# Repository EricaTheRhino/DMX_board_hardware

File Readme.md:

Hardware designs for Erica led controller
=========================================

Designs where made in eagle 6.4

Jumper options
--------------

SJ1/SJ2 used for DMX passthough if not populating second rs485 converter (U3)
SJ3 used for linking logic and led power systems together for use with a single power supply
SJ4 links return serial from TLC5940 to avr if wanted

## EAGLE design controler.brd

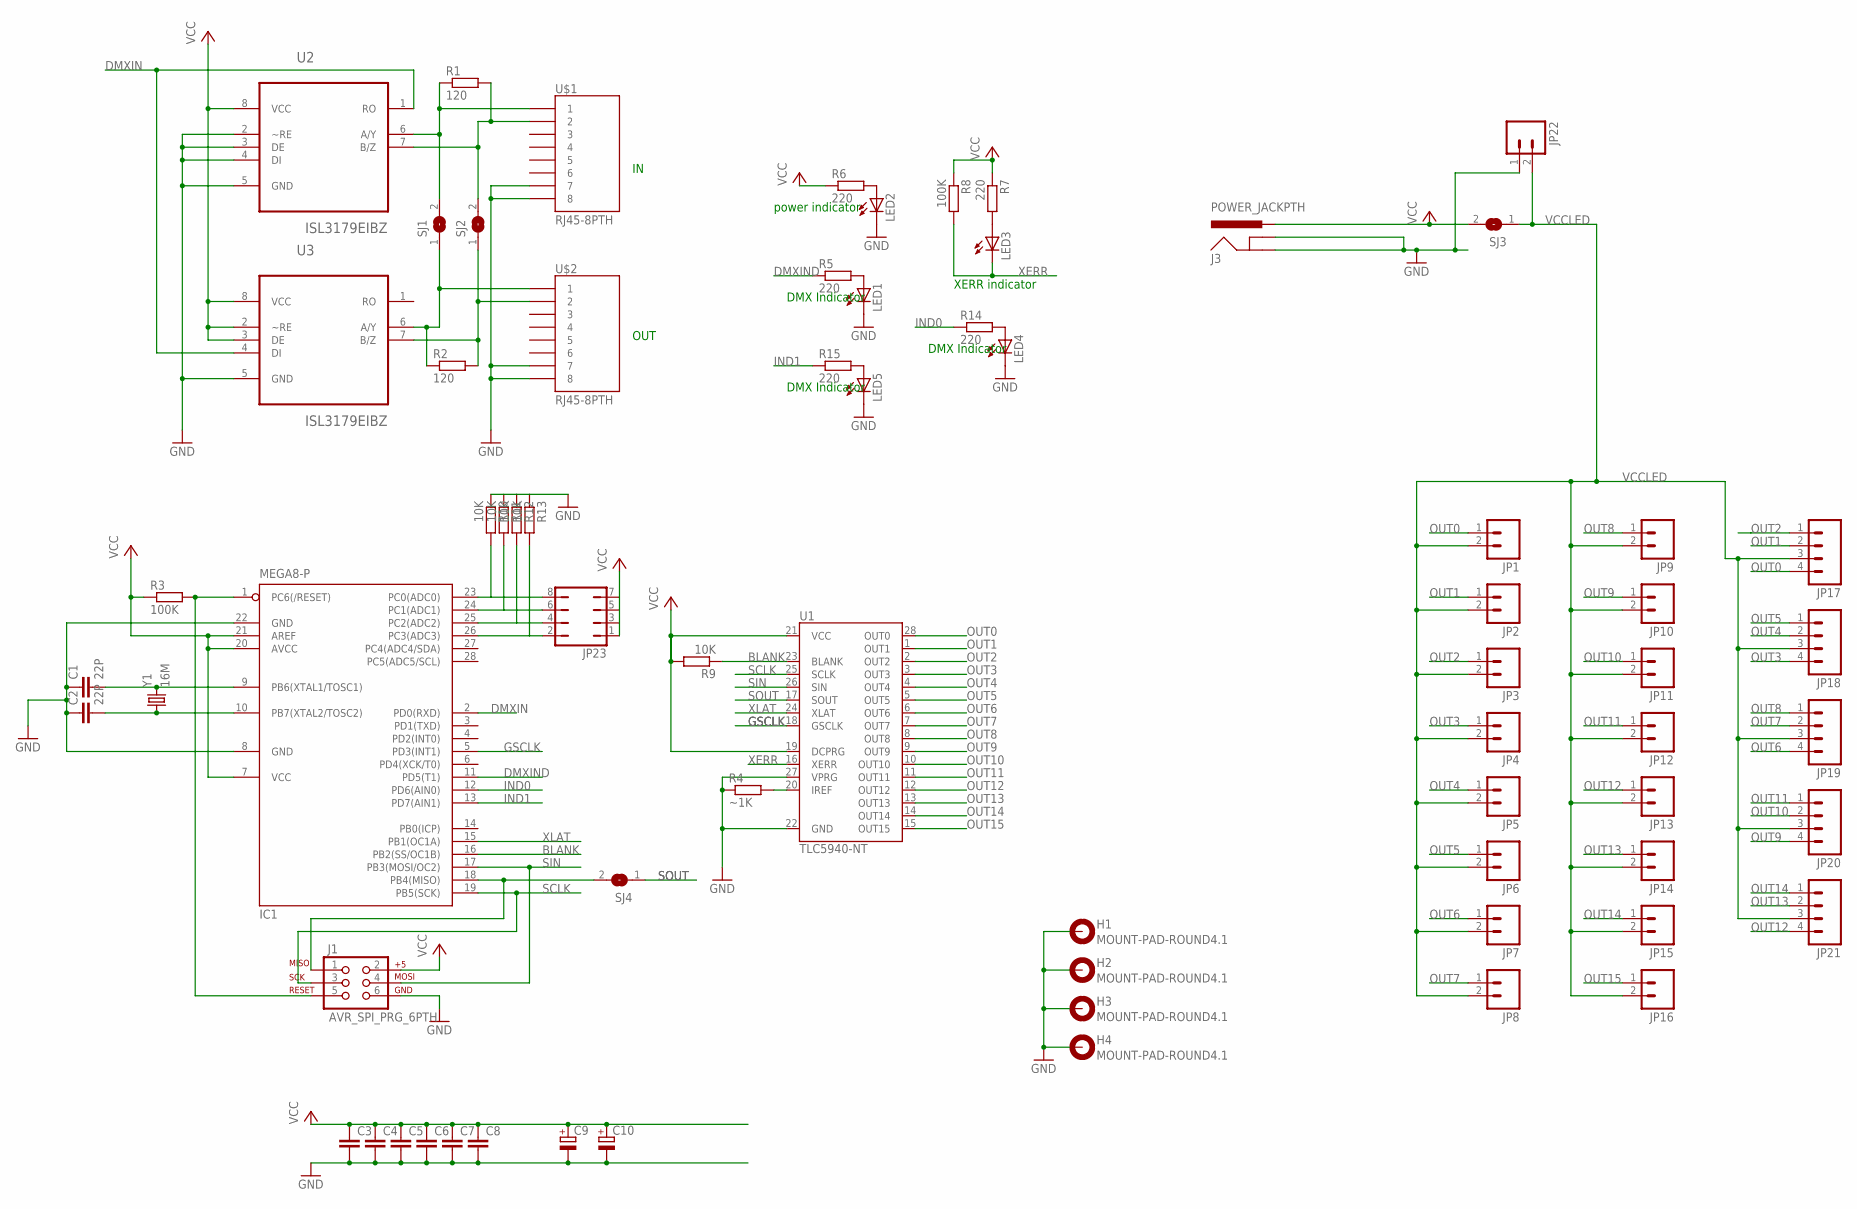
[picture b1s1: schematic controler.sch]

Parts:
C1, C2: 22P; C0603
C3, C4, C5, C6, C7, C8: C-EUC0603; C0603
C9: CPOL-EUE2.5-6; E2,5-6
C10: CPOL-EUE3.5-10; E3,5-10
H1, H2, H3, H4: MOUNT-PAD-ROUND4.1; 4,1-PAD
IC1: MEGA8-P; DIL28-3
J1: AVR_SPI_PRG_6PTH; 2X3
J3: POWER_JACKPTH; POWER_JACK_PTH
JP1, JP2, JP3, JP4, JP5, JP6, JP7, JP8, JP9, JP10, JP11, JP12, JP13, JP14, JP15, JP16: M02POLAR; MOLEX-1X2
JP17, JP18, JP19, JP20, JP21: M04POLAR; MOLEX-1X4
JP22: M023.5MM; SCREWTERMINAL-3.5MM-2
JP23: JP4Q
LED1, LED2, LED3, LED4, LED5: LEDCHIPLED_0603; CHIPLED_0603
R1, R2: 120; R0603
R3, R8: 100K; R0603
R4: ~1K; R0603
R5, R6, R7, R14, R15: 220; R0603
R9, R10, R11, R12, R13: 10K; R0603
SJ1, SJ2, SJ4: SJ
SJ3: SJW
U1: TLC5940-NT; DIL28-3
U2, U3: ISL3179EIBZ; SOIC127P600X175-8N
U$1, U$2: RJ45-8PTH; RJ45-8
Y1: 16M; HC49US

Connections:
BLANK: IC1.16 (PB2(SS/OC1B)), R9.1, U1.23 (BLANK)
DMXIN: IC1.2 (PD0(RXD)), U2.1 (RO), U3.4 (DI)
DMXIND: IC1.11 (PD5(T1)), R5.1
GND: C1.1, C2.1, C3.2, C4.2, C5.2, C6.2, C7.2, C8.2, C9.-, C10.-, H1.B4,1, H2.B4,1, H3.B4,1, H4.B4,1, IC1.8 (GND), IC1.22 (GND), J1.6, J3.GND, J3.GNDBREAK, JP22.1, LED1.C, LED2.C, LED4.C, LED5.C, R4.1, R10.1, R11.1, R12.1, R13.1, U1.22 (GND), U1.27 (VPRG), U2.2 (~RE), U2.3 (DE), U2.4 (DI), U2.5 (GND), U3.5 (GND), U$1.7, U$1.8, U$2.7, U$2.8
GSCLK: IC1.5 (PD3(INT1)), U1.18 (GSCLK)
IND0: IC1.12 (PD6(AIN0)), R14.1
IND1: IC1.13 (PD7(AIN1)), R15.1
unnamed: R1.1, SJ1.2, U2.6 (A/Y), U$1.1
unnamed: R1.2, SJ2.2, U2.7 (B/Z), U$1.2
unnamed: R2.1, SJ1.1, U3.6 (A/Y), U$2.1
unnamed: R2.2, SJ2.1, U3.7 (B/Z), U$2.2
unnamed: C1.2, IC1.9 (PB6(XTAL1/TOSC1)), Y1.2
unnamed: C2.2, IC1.10 (PB7(XTAL2/TOSC2)), Y1.1
unnamed: IC1.23 (PC0(ADC0)), JP23.8, R10.2
unnamed: IC1.24 (PC1(ADC1)), JP23.6, R11.2
unnamed: IC1.1 (PC6(/RESET)), J1.5, R3.2
unnamed: IC1.25 (PC2(ADC2)), JP23.4, R12.2
unnamed: IC1.18 (PB4(MISO)), J1.1, SJ4.2
unnamed: IC1.26 (PC3(ADC3)), JP23.2, R13.2
unnamed: LED5.A, R15.2
unnamed: R4.2, U1.20 (IREF)
unnamed: LED3.A, R7.2
unnamed: LED1.A, R5.2
unnamed: LED4.A, R14.2
unnamed: LED2.A, R6.2
OUT0: JP1.1, JP17.4, U1.28 (OUT0)
OUT1: JP2.1, JP17.2, U1.1 (OUT1)
OUT2: JP3.1, JP17.1, U1.2 (OUT2)
OUT3: JP4.1, JP18.4, U1.3 (OUT3)
OUT4: JP5.1, JP18.2, U1.4 (OUT4)
OUT5: JP6.1, JP18.1, U1.5 (OUT5)
OUT6: JP7.1, JP19.4, U1.6 (OUT6)
OUT7: JP8.1, JP19.2, U1.7 (OUT7)
OUT8: JP9.1, JP19.1, U1.8 (OUT8)
OUT9: JP10.1, JP20.4, U1.9 (OUT9)
OUT10: JP11.1, JP20.2, U1.10 (OUT10)
OUT11: JP12.1, JP20.1, U1.11 (OUT11)
OUT12: JP13.1, JP21.4, U1.12 (OUT12)
OUT13: JP14.1, JP21.2, U1.13 (OUT13)
OUT14: JP15.1, JP21.1, U1.14 (OUT14)
OUT15: JP16.1, U1.15 (OUT15)
SCLK: IC1.19 (PB5(SCK)), J1.3, U1.25 (SCLK)
SIN: IC1.17 (PB3(MOSI/OC2)), J1.4, U1.26 (SIN)
SOUT: SJ4.1, U1.17 (SOUT)
VCC: C3.1, C4.1, C5.1, C6.1, C7.1, C8.1, C9.+, C10.+, IC1.7 (VCC), IC1.20 (AVCC), IC1.21 (AREF), J1.2, J3.PWR, JP23.1, JP23.3, JP23.5, JP23.7, R3.1, R6.1, R7.1, R8.1, R9.2, SJ3.2, U1.19 (DCPRG), U1.21 (VCC), U2.8 (VCC), U3.2 (~RE), U3.3 (DE), U3.8 (VCC)
VCCLED: JP1.2, JP2.2, JP3.2, JP4.2, JP5.2, JP6.2, JP7.2, JP8.2, JP9.2, JP10.2, JP11.2, JP12.2, JP13.2, JP14.2, JP15.2, JP16.2, JP17.3, JP18.3, JP19.3, JP20.3, JP21.3, JP22.2, SJ3.1
XERR: LED3.C, R8.2, U1.16 (XERR)
XLAT: IC1.15 (PB1(OC1A)), U1.24 (XLAT)

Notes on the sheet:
OUT
DMX Indicator
power indicator
XERR indicator

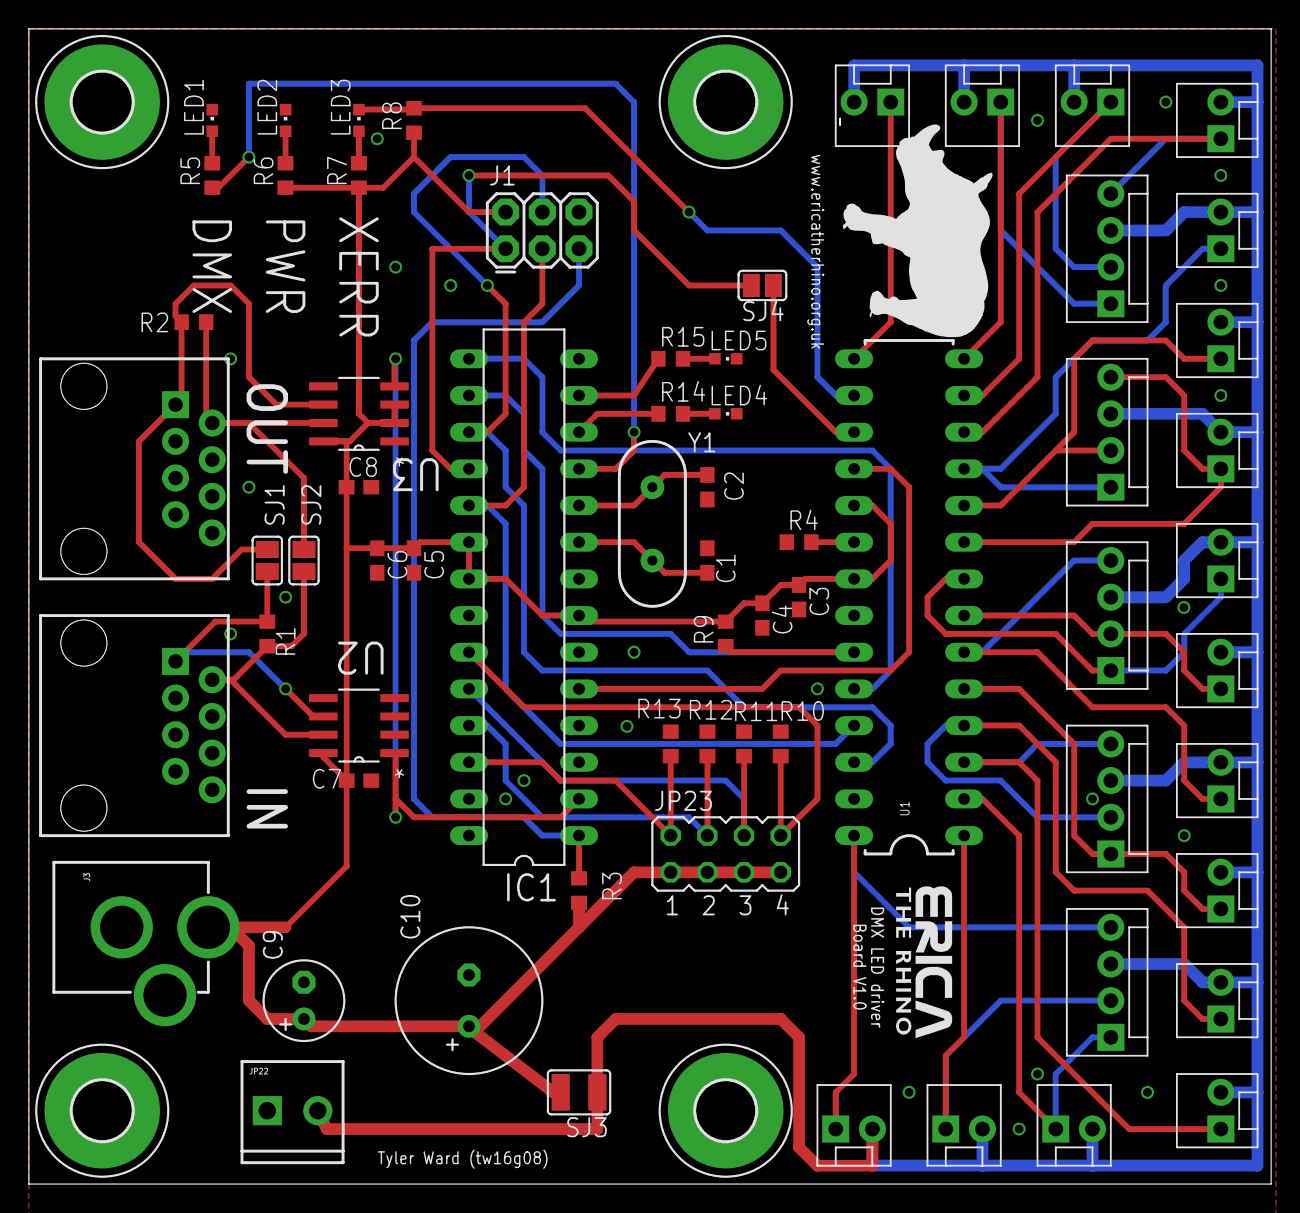
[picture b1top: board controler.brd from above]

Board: 2 copper layers, 86.0 x 80.0 mm, 70 parts (0 on the bottom side), 48 nets.

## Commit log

2014-03-17 Added V1.0 Eagle designs for led controler.
2014-03-17 Added readme and .gitignore

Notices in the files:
parts and their libraries:
SparkFun: Licensing: CC v3.0 Share-Alike You are welcome to use this library for commercial purposes.
